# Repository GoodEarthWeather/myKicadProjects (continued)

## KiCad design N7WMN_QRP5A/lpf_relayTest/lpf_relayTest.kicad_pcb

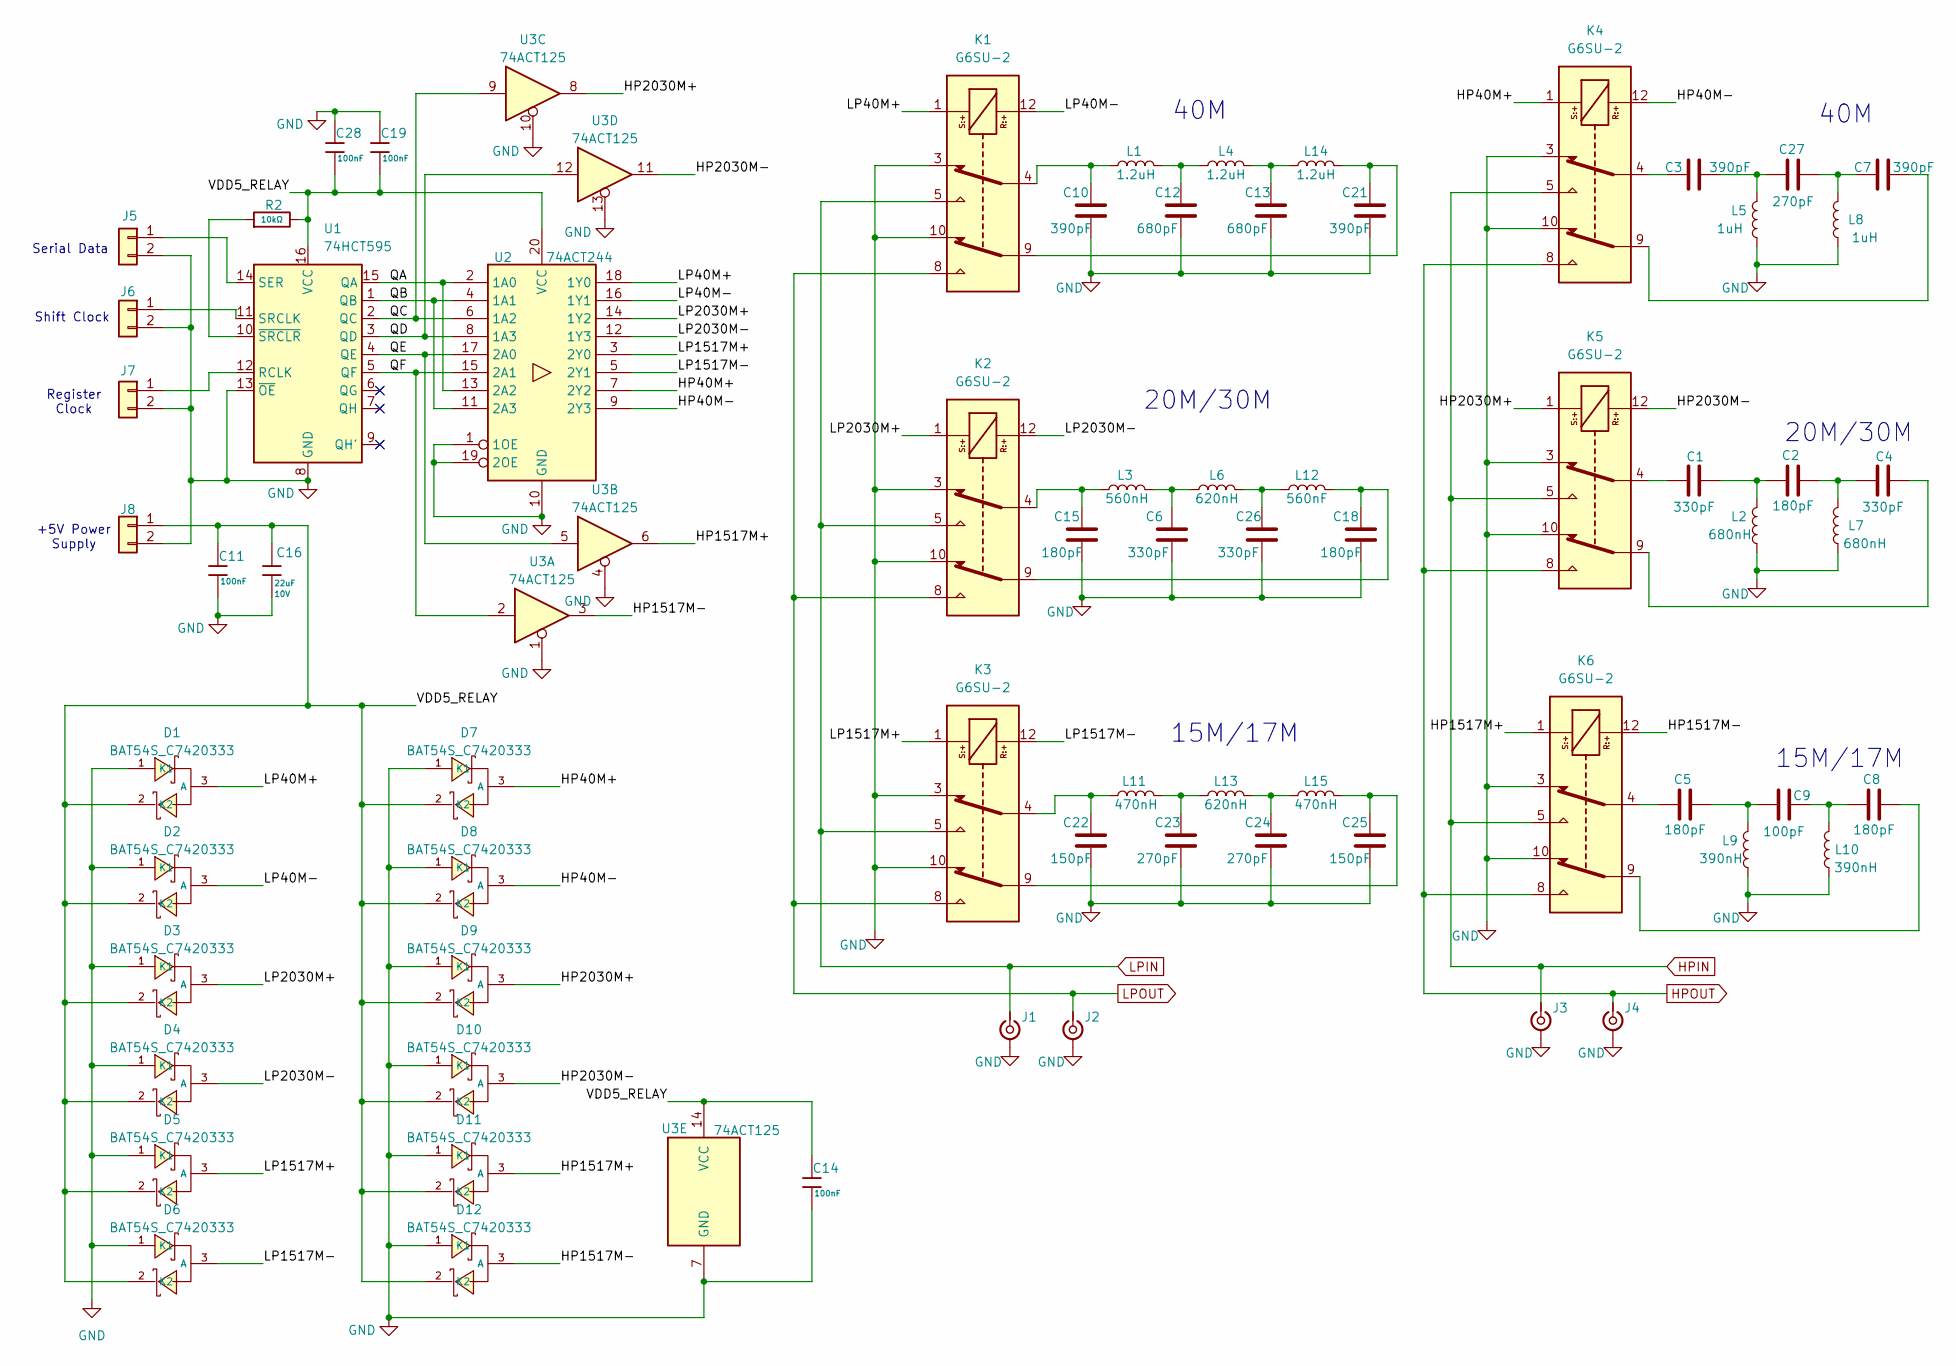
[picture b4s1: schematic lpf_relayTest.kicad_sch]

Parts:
C1, C4, C6, C26: 330pF; C_0805_2012Metric_Pad1.18x1.45mm_HandSolder; jlcpcb C113820
C2, C5, C8, C15, C18: 180pF; C_0805_2012Metric_Pad1.18x1.45mm_HandSolder; jlcpcb C527205
C3, C7, C10, C21: 390pF; C_0805_2012Metric_Pad1.18x1.45mm_HandSolder; jlcpcb C527206
C9: 100pF; C_0805_2012Metric_Pad1.18x1.45mm_HandSolder; jlcpcb C107105
C11, C14, C19, C28: 100nF; C_0603; Voltage Rated 50V; Tolerance ±10%; Part CC0603KRX7R9BB104; LCSC C14663
C12, C13: 680pF; C_0805_2012Metric_Pad1.18x1.45mm_HandSolder; jlcpcb C513601
C16: 22uF; C_1206; Voltage Rated 10V; Tolerance ±10%; Part CL31A226KPHNNNE; LCSC C5672
C22, C25: 150pF; C_0805_2012Metric_Pad1.18x1.45mm_HandSolder; jlcpcb C576916
C23, C24, C27: 270pF; C_0805_2012Metric_Pad1.18x1.45mm_HandSolder; jlcpcb C107106
D1, D2, D3, D4, D5, D6, D7, D8, D9, D10, D11, D12: BAT54S_C7420333; SOT-23-3_L2.9-W1.3-P1.90-LS2.4-BR; Reverse Voltage (Vr) 30V; Forward Voltage (Vf@If) 0.4V@10mA; Part BAT54S; LCSC C7420333
J1, J2, J3, J4: Conn_Coaxial_Small; SMA_Samtec_SMA-J-P-H-ST-EM1_EdgeMount
J5, J6, J7, J8: Conn_01x02; PinHeader_1x02_P2.54mm_Vertical
K1, K2, K3, K4, K5, K6: G6SU-2; Relay_DPDT_Omron_G6S-2F; Mouser Part Number 653-G6SU-2F-TRDC5
L1, L4, L14: 1.2uH; L_Toroid_Vertical_L13.0mm_W6.5mm_P5.60mm
L2, L7: 680nH; L_Toroid_Vertical_L13.0mm_W6.5mm_P5.60mm
L3: 560nH; L_Toroid_Vertical_L13.0mm_W6.5mm_P5.60mm
L5, L8: 1uH; L_Toroid_Vertical_L13.0mm_W6.5mm_P5.60mm
L6, L13: 620nH; L_Toroid_Vertical_L13.0mm_W6.5mm_P5.60mm
L9, L10: 390nH; L_Toroid_Vertical_L13.0mm_W6.5mm_P5.60mm
L11, L15: 470nH; L_Toroid_Vertical_L13.0mm_W6.5mm_P5.60mm
L12: 560nF; L_Toroid_Vertical_L13.0mm_W6.5mm_P5.60mm
R2: 10kΩ; R_0603; Overload Voltage (Max) 75V; Tolerance ±1%; Part 0603WAF1002T5E; LCSC C25804
U1: 74HCT595; SOIC-16_3.9x9.9mm_P1.27mm; jlcpcb C842450
U2: 74ACT244; TSSOP-20_4.4x6.5mm_P0.65mm; jlcpcb C6930
U3: 74ACT125; SOIC-14_3.9x8.7mm_P1.27mm; jlcpcb C113254

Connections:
/HP40M+: D7.3 (A), K4.1, U2.7 (2Y2)
/HP40M-: D8.3 (A), K4.12, U2.9 (2Y3)
/HP1517M+: D11.3 (A), K6.1, U3.6
/HP1517M-: D12.3 (A), K6.12, U3.3
/HP2030M+: D9.3 (A), K5.1, U3.8
/HP2030M-: D10.3 (A), K5.12, U3.11
/LP40M+: D1.3 (A), K1.1, U2.18 (1Y0)
/LP40M-: D2.3 (A), K1.12, U2.16 (1Y1)
/LP1517M+: D5.3 (A), K3.1, U2.3 (2Y0)
/LP1517M-: D6.3 (A), K3.12, U2.5 (2Y1)
/LP2030M+: D3.3 (A), K2.1, U2.14 (1Y2)
/LP2030M-: D4.3 (A), K2.12, U2.12 (1Y3)
/QA: U1.6 (QG), U1.15 (QA), U2.2 (1A0), U2.13 (2A2)
/QB: U1.1 (QB), U1.7 (QH), U2.4 (1A1), U2.11 (2A3)
/QC: U1.2 (QC), U2.6 (1A2), U3.9
/QD: U1.3 (QD), U2.8 (1A3), U3.12
/QE: U1.4 (QE), U2.17 (2A0), U3.5
/QF: U1.5 (QF), U2.15 (2A1), U3.2
/VDD5_RELAY: C11.1, C14.1, C16.1, C19.2, C28.2, D1.2 (K2), D2.2 (K2), D3.2 (K2), D4.2 (K2), D5.2 (K2), D6.2 (K2), D7.2 (K2), D8.2 (K2), D9.2 (K2), D10.2 (K2), D11.2 (K2), D12.2 (K2), J8.1, R2.2, U1.16 (VCC), U2.20 (VCC), U3.14 (VCC)
GND: C6.2, C10.2, C11.2, C12.2, C13.2, C14.2, C15.2, C16.2, C18.2, C19.1, C21.2, C22.2, C23.2, C24.2, C25.2, C26.2, C28.1, D1.1 (K1), D2.1 (K1), D3.1 (K1), D4.1 (K1), D5.1 (K1), D6.1 (K1), D7.1 (K1), D8.1 (K1), D9.1 (K1), D10.1 (K1), D11.1 (K1), D12.1 (K1), J1.2 (Ext), J2.2 (Ext), J3.2 (Ext), J4.2 (Ext), J5.2, J6.2, J7.2, J8.2, K1.3, K1.10, K2.3, K2.10, K3.3, K3.10, K4.3, K4.10, K5.3, K5.10, K6.3, K6.10, L2.2, L5.2, L7.2, L8.2, L9.2, L10.2, U1.8 (GND), U1.13 (~OE), U2.1 (1OE), U2.10 (GND), U2.19 (2OE), U3.1, U3.4, U3.7 (GND), U3.10, U3.13
HPIN: J3.1 (In), K4.5, K5.5, K6.5
HPOUT: J4.1 (In), K4.8, K5.8, K6.8
LPIN: J1.1 (In), K1.5, K2.5, K3.5
LPOUT: J2.1 (In), K1.8, K2.8, K3.8
unnamed: C1.1, K5.4
unnamed: C1.2, C2.1, L2.1
unnamed: C2.2, C4.1, L7.1
unnamed: C3.1, K4.4
unnamed: C4.2, K5.9
unnamed: C5.1, K6.4
unnamed: C5.2, C9.2, L9.1
unnamed: C6.1, L3.2, L6.1
unnamed: C7.2, K4.9
unnamed: C8.1, C9.1, L10.1
unnamed: C8.2, K6.9
unnamed: C10.1, K1.4, L1.1
unnamed: C12.1, L1.2, L4.1
unnamed: C13.1, L4.2, L14.1
unnamed: C15.1, K2.4, L3.1
unnamed: C18.1, K2.9, L12.2
unnamed: C21.1, K1.9, L14.2
unnamed: C22.1, K3.4, L11.1
unnamed: C23.1, L11.2, L13.1
unnamed: C24.1, L13.2, L15.1
unnamed: C25.1, K3.9, L15.2
unnamed: C26.1, L6.2, L12.1
unnamed: C3.2, C27.1, L5.1
unnamed: C7.1, C27.2, L8.1
unnamed: J5.1, U1.14 (SER)
unnamed: J6.1, U1.11 (SRCLK)
unnamed: J7.1, U1.12 (RCLK)
unnamed: R2.1, U1.10 (~SRCLR)

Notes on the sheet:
15M/17M
Serial Data
Register Clock
Shift Clock
20M/30M
40M
+5V Power Supply

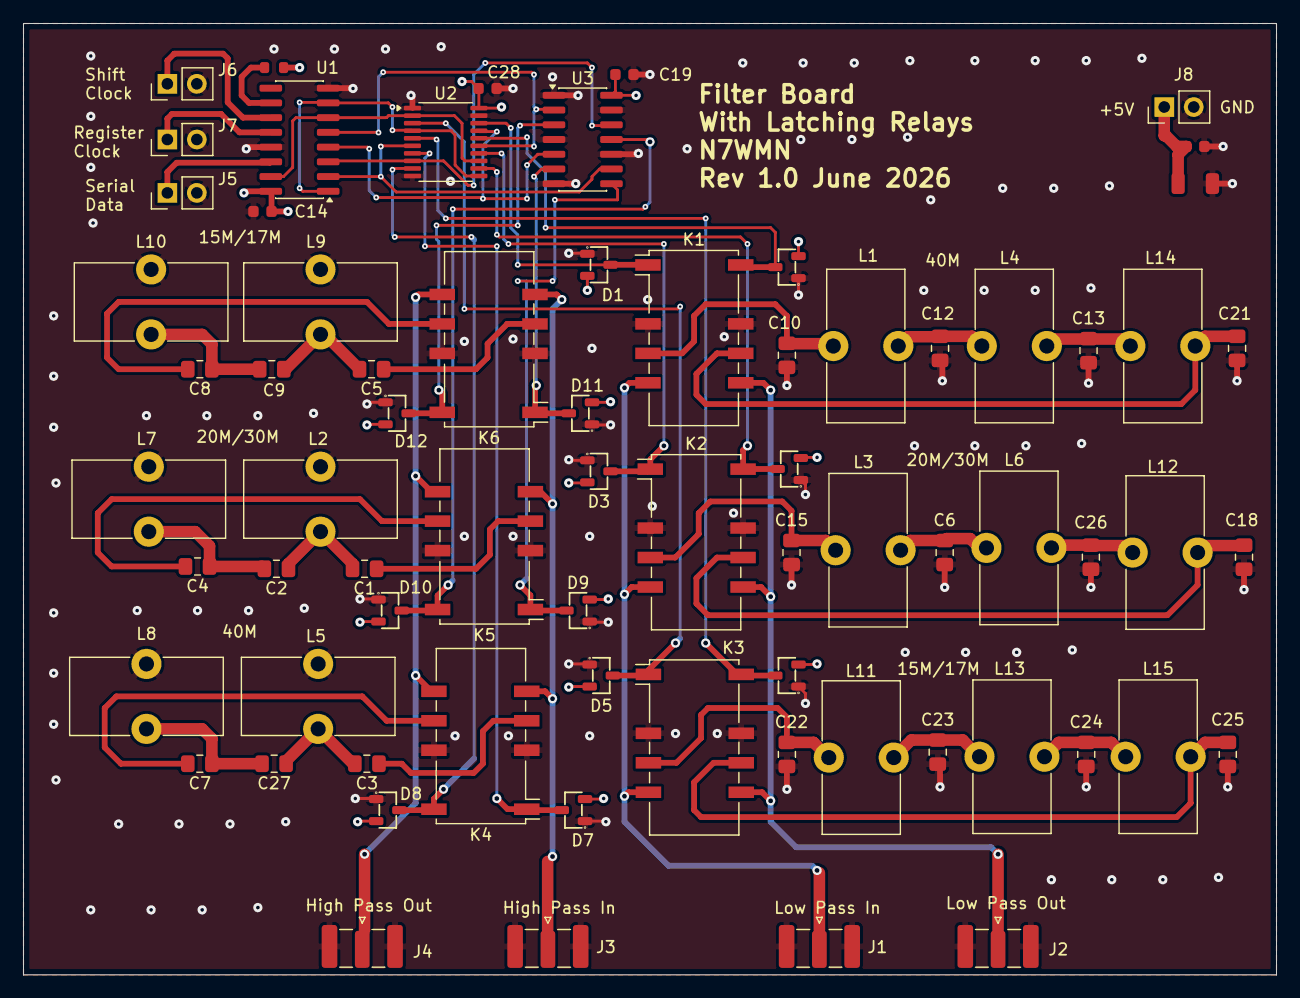
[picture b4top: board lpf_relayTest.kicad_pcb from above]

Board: 4 copper layers, 108.0 x 82.0 mm, 71 parts (0 on the bottom side), 52 nets.

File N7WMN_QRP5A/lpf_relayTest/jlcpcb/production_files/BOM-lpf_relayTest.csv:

Comment,Designator,Footprint,LCSC,Quantity
100nF,"C11,C14,C19,C28",C_0603,C14663,4
100pF,C9,C_0805_2012Metric_Pad1.18x1.45mm_HandSolder,C107105,1
10kΩ,R2,R_0603,C25804,1
150pF,"C22,C25",C_0805_2012Metric_Pad1.18x1.45mm_HandSolder,C576916,2
180pF,"C15,C18,C2,C5,C8",C_0805_2012Metric_Pad1.18x1.45mm_HandSolder,C527205,5
22uF,C16,C_1206,C5672,1
270pF,"C23,C24,C27",C_0805_2012Metric_Pad1.18x1.45mm_HandSolder,C107106,3
330pF,"C1,C26,C4,C6",C_0805_2012Metric_Pad1.18x1.45mm_HandSolder,C113820,4
390pF,"C10,C21,C3,C7",C_0805_2012Metric_Pad1.18x1.45mm_HandSolder,C527206,4
680pF,"C12,C13",C_0805_2012Metric_Pad1.18x1.45mm_HandSolder,C513601,2
74ACT125,U3,SOIC-14_3.9x8.7mm_P1.27mm,C113254,1
74ACT244,U2,TSSOP-20_4.4x6.5mm_P0.65mm,C6930,1
74HC595,U1,SOIC-16_3.9x9.9mm_P1.27mm,C10092,1
BAT54S_C7420333,"D1,D10,D11,D12,D2,D3,D4,D5,D6,D7,D8,D9",SOT-23-3_L2.9-W1.3-P1.90-LS2.4-BR,C7420333,12
G6SU-2,"K1,K2,K3,K4,K5,K6",Relay_DPDT_Omron_G6S-2F,C1560948,6

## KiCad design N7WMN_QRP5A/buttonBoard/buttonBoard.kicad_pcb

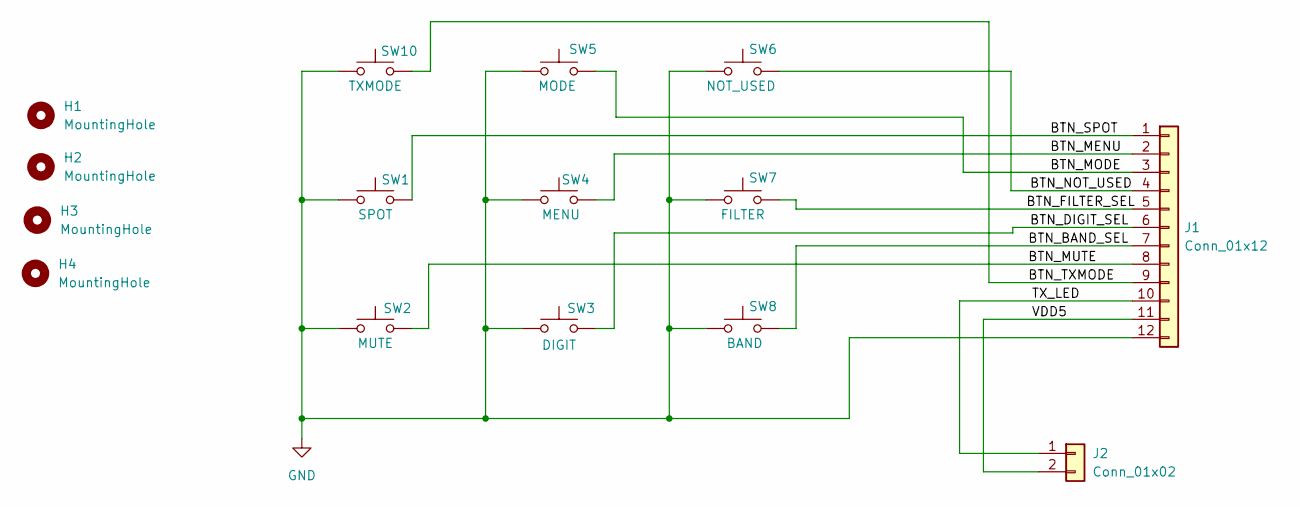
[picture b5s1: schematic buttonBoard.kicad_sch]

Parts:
H1, H2, H3, H4: MountingHole; MountingHole_3.2mm_M3
J1: Conn_01x12; PinHeader_1x12_P2.54mm_Horizontal
J2: Conn_01x02; PinHeader_1x02_P2.54mm_Horizontal
SW1: SPOT; SW_PUSH-12mm
SW2: MUTE; SW_PUSH-12mm
SW3: DIGIT; SW_PUSH-12mm
SW4: MENU; SW_PUSH-12mm
SW5: MODE; SW_PUSH-12mm
SW6: NOT_USED; SW_PUSH-12mm
SW7: FILTER; SW_PUSH-12mm
SW8: BAND; SW_PUSH-12mm
SW10: TXMODE; SW_PUSH-12mm

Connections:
/BTN_BAND_SEL: J1.7, SW8.2
/BTN_DIGIT_SEL: J1.6, SW3.2
/BTN_FILTER_SEL: J1.5, SW7.2
/BTN_MENU: J1.2, SW4.2
/BTN_MODE: J1.3, SW5.2
/BTN_MUTE: J1.8, SW2.2
/BTN_NOT_USED: J1.4, SW6.2
/BTN_SPOT: J1.1, SW1.2
/BTN_TXMODE: J1.9, SW10.2
/TX_LED: J1.10, J2.1
/VDD5: J1.11, J2.2
GND: J1.12, SW1.1, SW2.1, SW3.1, SW4.1, SW5.1, SW6.1, SW7.1, SW8.1, SW10.1

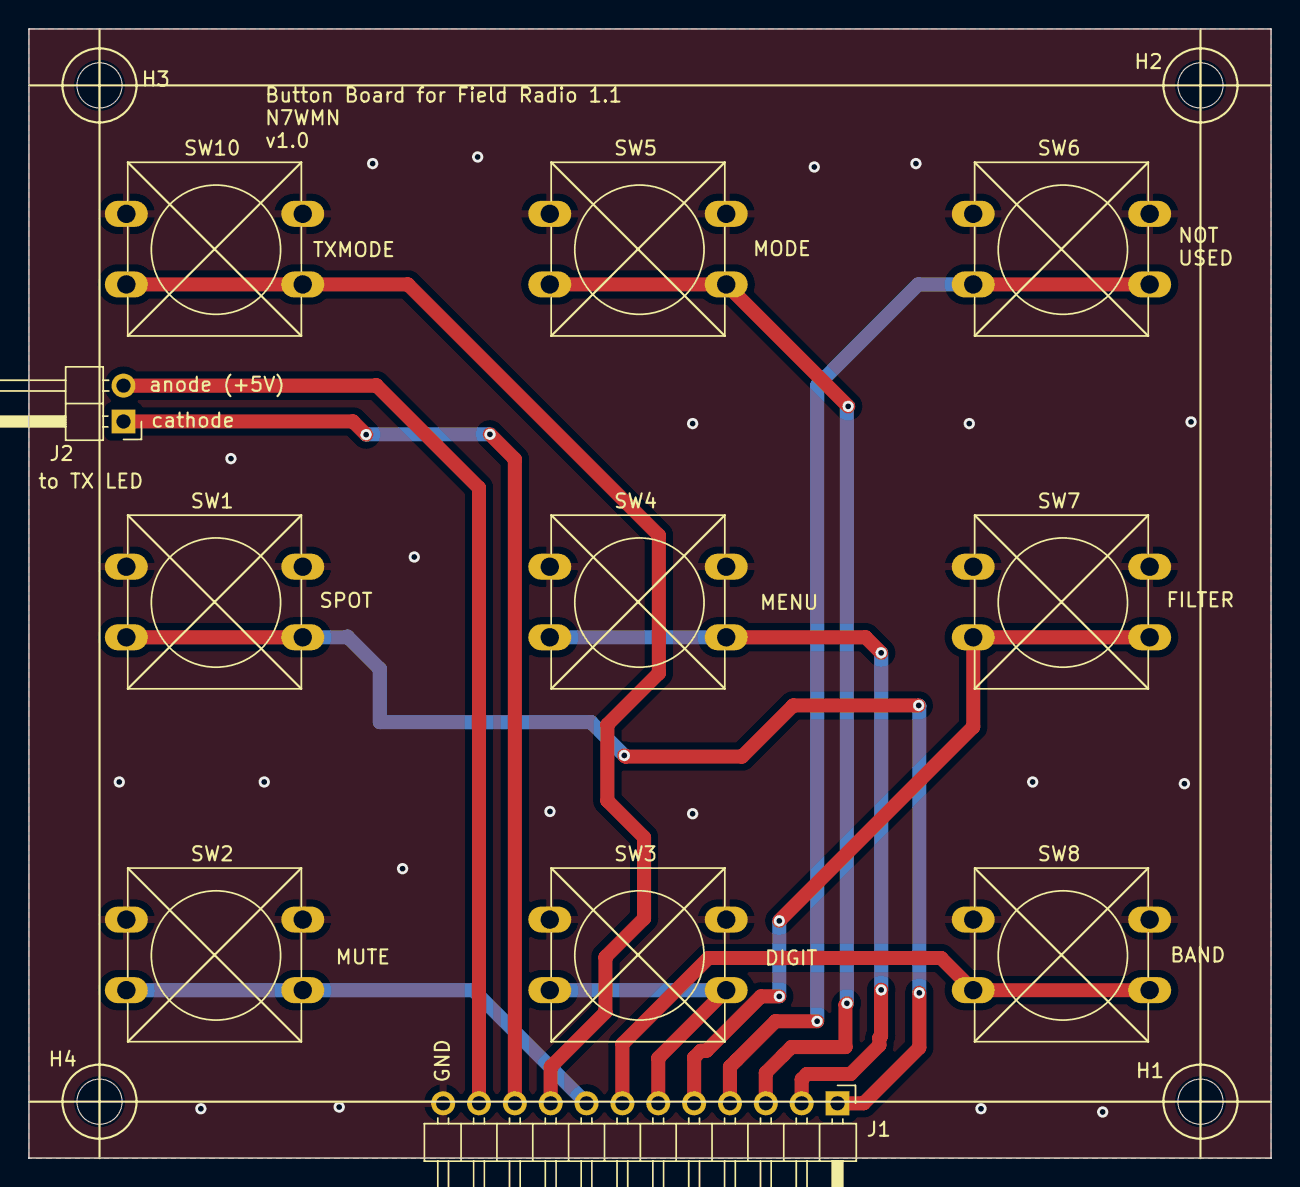
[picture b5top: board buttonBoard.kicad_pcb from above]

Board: 2 copper layers, 88.0 x 80.0 mm, 15 parts (0 on the bottom side), 12 nets.

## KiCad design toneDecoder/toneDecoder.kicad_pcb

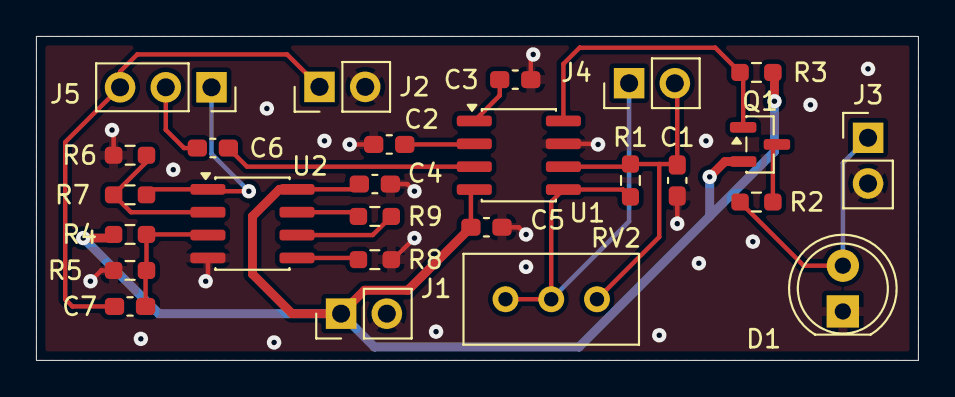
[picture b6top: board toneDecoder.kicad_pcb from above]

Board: 2 copper layers, 49.0 x 18.0 mm, 26 parts (0 on the bottom side), 18 nets.

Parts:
C1, C5: 0.1uF; C_0603_1608Metric_Pad1.08x0.95mm_HandSolder
C2: 2.2uF; C_0603_1608Metric_Pad1.08x0.95mm_HandSolder
C3, C4: 4.7uF; C_0603_1608Metric_Pad1.08x0.95mm_HandSolder
C6, C7: 1uF; C_0603_1608Metric_Pad1.08x0.95mm_HandSolder
D1: LED_Small; LED_D5.0mm
J1, J2, J3, J4: Conn_01x02; PinHeader_1x02_P2.54mm_Vertical
J5: Conn_01x03; PinSocket_1x03_P2.54mm_Vertical
Q1: BSS84; SOT-23
R1, R4, R5, R6, R7, R8, R9: 15K; R_0603_1608Metric_Pad0.98x0.95mm_HandSolder
R2: 560; R_0603_1608Metric_Pad0.98x0.95mm_HandSolder
R3: 10K; R_0603_1608Metric_Pad0.98x0.95mm_HandSolder
RV2: R_Potentiometer; Potentiometer_Bourns_3386C_Horizontal
U1: NE567; SOIC-8_3.9x4.9mm_P1.27mm
U2: OPA1678; SOIC-8_3.9x4.9mm_P1.27mm

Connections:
/VDD5: C4.1, C5.1, J1.1, Q1.2 (S), R3.2, R4.2, U1.4 (VCC), U2.8 (V+)
/a_input: C6.2, J5.2
/audio_filt_in: J5.1, R7.1, U2.1
/audio_in: C7.2, J2.1, J5.3
/detect_out: D1.2 (A), J3.1, R2.1
/dout: Q1.1 (G), R3.1, U1.8 (OUTPUT)
GND: C1.2, C2.2, C3.2, C4.2, C5.2, D1.1 (K), J1.2, J2.2, J3.2, R5.1, R6.1, R8.2, U1.7 (GND), U2.4 (V-)
unnamed: J4.1, R1.1, RV2.1, RV2.2, U1.5 (TIM_R)
unnamed: C1.1, J4.2, R1.2, RV2.3, U1.6 (TIM_RC)
unnamed: Q1.3 (D), R2.2
unnamed: R9.1, U2.7
unnamed: C6.1, U1.3 (INPUT)
unnamed: C2.1, U1.2 (LP_FLT_C)
unnamed: C3.1, U1.1 (OFLT_C)
unnamed: C7.1, R4.1, R5.2, U2.3 (+)
unnamed: R6.2, R7.2, U2.2 (-)
unnamed: R8.1, U2.5 (+)
unnamed: R9.2, U2.6 (-)

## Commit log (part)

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2022-03-25 Initialialization
    Initial setup of repository
2022-03-25 Board Tape Out
    Final tapeout changes; board ordered
2022-03-29 added ignore file
    cosmetic changes; added ignore file
2022-05-16 Update
    Committing pcb/schematic updates
2022-10-07 Update .gitignore
    ignore zip files
2022-10-07 Removed zip files
    remove zip files
2022-10-07 Create .gitignore
    remove zip files
2022-10-12 Initial completion of schematic and routing
    Routing complete; first pass
2022-10-24 Add new LPF Board
    first pass of CWAZ low pass filter board
2022-10-25 first pass layout
    first pass layout complete and ready to tape out
2022-10-27 Final Tape Out Versions
    final version for tapeout
2022-11-13 Corrected LPF; add Preselector
    Fixed circuit design error on LPF regarding relay connections; first pass at adding preselctor schematic
2022-11-18 Added T/R Switch
    Added T/R switch and updated preselector.
2022-11-19 TRSwitch - added resistor
    Added 10K resistors to reduce current in bias switching
2022-11-22 Final versions of preselector, tr-switch, si514
    Tape out versions of TR switch, preselector and si514 clock board
2022-12-22 Updated schematics and layout
    Updated T/R switch to rev. B after lab tests
2022-12-27 Rev. C of Tayloe Detector/QSD
    New rev of QSD detector and updates to TR switch
2022-12-28 Tape Out of T/RBoard and QSD
    Rev. B of T/R board and Rev. C of Tayloe detector board
2022-12-29 Audio block
    Start of board to combine all pass and lp-hp filters
2023-01-01 Start allpass+filters
    Initial commit of board combining allpass and hp, lp filters
2023-01-02 Initial Placement
    Initial placement of audio filter board
2023-01-03 First Pass Routing
    first pass routing of audio filter board
2023-01-03 audioFilters board tapeout
    ready for tapeout
2023-01-04 RF Att Board
    completed schematic/layout ready for tapeout
2023-01-04 Made gerbers for boards
    gerbers for attenuator and audio filters boards
2023-01-13 Update Audio Board
    modify design and layout improvements
2023-01-16 Tapeout - audio and power boards
    Last mods to audio board; new power board
2024-03-06 Resync to Windows10
    Getting synced to github with Windows10 laptop
2024-03-10 In progress
    building schematic
2024-03-10 ready for layout
    footprint assignment should be complete
2024-03-10 initial placement
    first placement for pcb
2024-03-13 Tape Out Power Amp
    First tape out of power amp board
2024-03-26 Start of OptiLowPass Filter
    New design to fix low pass board routing problem (unwanted coupling) and to change from CWAZ to OptiLowPass.
2024-03-27 First Tapeout
    First tapeout of AptLowPass to JLCPCB
2024-04-01 Field Radio First Pass
    Starting assembly of field radio schematics
2024-04-04 Updated OptLowPass schematic
    Change to SMD caps and prepare for final layout
2024-04-06 Ready for tapeout
    Filter board now with diode switching and SMD caps; power amp board updated with beefier dual nmos.
2024-04-09 Building fieldradio schematic
    in process of building field radio schematics
2024-04-16 Updating field radio
    Continued schematic work on field radio
2024-04-19 More schematic dev.
    More schematic development
2024-04-23 Tapeout PowerAmp and QSD
    PowerAmp rev. C and QSD rev. D
2024-05-22 Update Connectors
    Changed to PCB mount connectors for back panel
2024-05-26 Clean Up
    Schematic clean up in prep for layout
2024-05-28 Placement Update
    LPF and TR Switch placed
2024-05-30 Placement of preselector and qsd
    Finished placement of these two blocks
2024-06-01 Finished Groups
    Blocks are placed
2024-06-02 Initial Block Placement
    Initial blocks are placed roughly
2024-06-05 Placement Refinement 1
    Ungrouping blocks and optimizing placement
2024-06-05 Refine Placement 2
    Finish refining block placement; ready for initial routing work.
2024-06-06 Routing Work 1
    Routing blocks
2024-06-08 Routing
    Continuing to route blocks
2024-06-09 More routing
    Detail routing work
2024-06-10 more detail routing
    detail routing
2024-06-10 First completed route
    no unconnected routes
2024-06-11 DRC cleanup
    DRC violation fixing
2024-06-12 First Clean DRC
    first clean drc
2024-06-14 Added support for unused gpio
    Also added option for external clock generator.
2024-11-22 finished movement of lcd
    Changed lcd connector to move closer to left hand side
2024-11-23 Final Gerbers - 1
    Release of final gerbers for first fab
2024-11-24 Tapeout for Field Radio and Preamp
    Field radio tapeout
    Also, preamp for loop antenna also tapeout
2024-12-23 Updated 25MHz crystal value
    Did calibration of si5351 to adjust value of 25MHz crystal to get correct output frequency.
2025-01-05 Started Rev. 1 of field radio
    Started rev of field radio based on results from first turn of board.
2025-01-14 Rev 1.1 layout update
    layout update routing and placement
2025-01-15 More layout updates
    DRC fixes
2025-01-16 Added PTT and TP for clocks
    More layout cleanup and tuning.
2025-01-18 Button Board
    added button board
2025-01-18 Tapeout Files
    button board and v1.1 radio tapeout files for JLCPCB
2025-03-15 Fix TR Switch Glitch
    Made changes to TR switch to reduce transients when switching.
2025-09-30 Added QEX power amp
    Added project for the QEX power amplifier experiment board.
2025-10-31 Updating and more schematic design
2025-10-31 Schematic work
2025-11-04 Continued schematic updates.
2025-11-12 Further work on schematic
2025-11-13 More schematic development
2025-11-13 Trying to re-sync after computer crash
2025-11-15 trying to clean this up
2025-11-15 Correct directory to push to github
2025-11-15 More cleanup
2025-11-16 Starting layout work
2025-11-17 Starting layout connections
2025-11-17 First pass of completed routing
2025-11-18 Layout refinement
2025-11-19 Clean DRC
2025-12-02 Refining layout
2025-12-04 Final PCB and BOM changes before tapeout
2026-02-07 Adding boost converter to projects.
2026-02-07 Finished boost converter and sent to fab.
2026-02-13 adding version 2 of the QEX amplifier project
2026-02-13 adding QEX amplifier project version 2
2026-02-17 Start version 2 of QEX amplifier
2026-02-18 Started layout of rev2 of QEX amplifier
2026-02-19 Layout first pass with 0 unrouted.
2026-02-27 Layout cleanup and refining
2026-02-28 Added jlcpcb part numbers
2026-03-03 Taped Out package to JLCPCB
2026-03-04 Corrected U2 footprint for jlcpcb; re-submitting
2026-03-04 First commit for FDIM project
2026-03-04 Updating layout
2026-03-05 Final tapeout
2026-03-15 clean up schematic to match workbench changes
2026-03-20 Updating FDIM board schematic
2026-03-24 changed specification of output transformer
2026-03-30 Adjustments to v2 QEX amplifier
2026-03-30 Adding circuit for swr protection
2026-03-30 Tapeout of swr protection circuit
2026-05-29 Starting to update fieldRadio 1.2 schematics
2026-05-29 schematic audio work on the audio path
2026-05-31 Finished first pass of audio schematic changes for binaural/mono
2026-05-31 Added new power output amp changes from QEX
2026-06-01 Adding schematic for relay testing with lpf
2026-06-02 more schematic work on this design
2026-06-03 finish first pass of relay test board; need more
2026-06-05 finished relay schematic; ready for layout
2026-06-09 completed first pass placement.
2026-06-12 working on layout of relayTest
2026-06-14 Relay Boarc Layout complete
2026-06-14 first pass schematic for tonedecoder
2026-06-22 tone decoder layout done
2026-06-27 updated swr schematic and board
2026-06-28 swr protection final
